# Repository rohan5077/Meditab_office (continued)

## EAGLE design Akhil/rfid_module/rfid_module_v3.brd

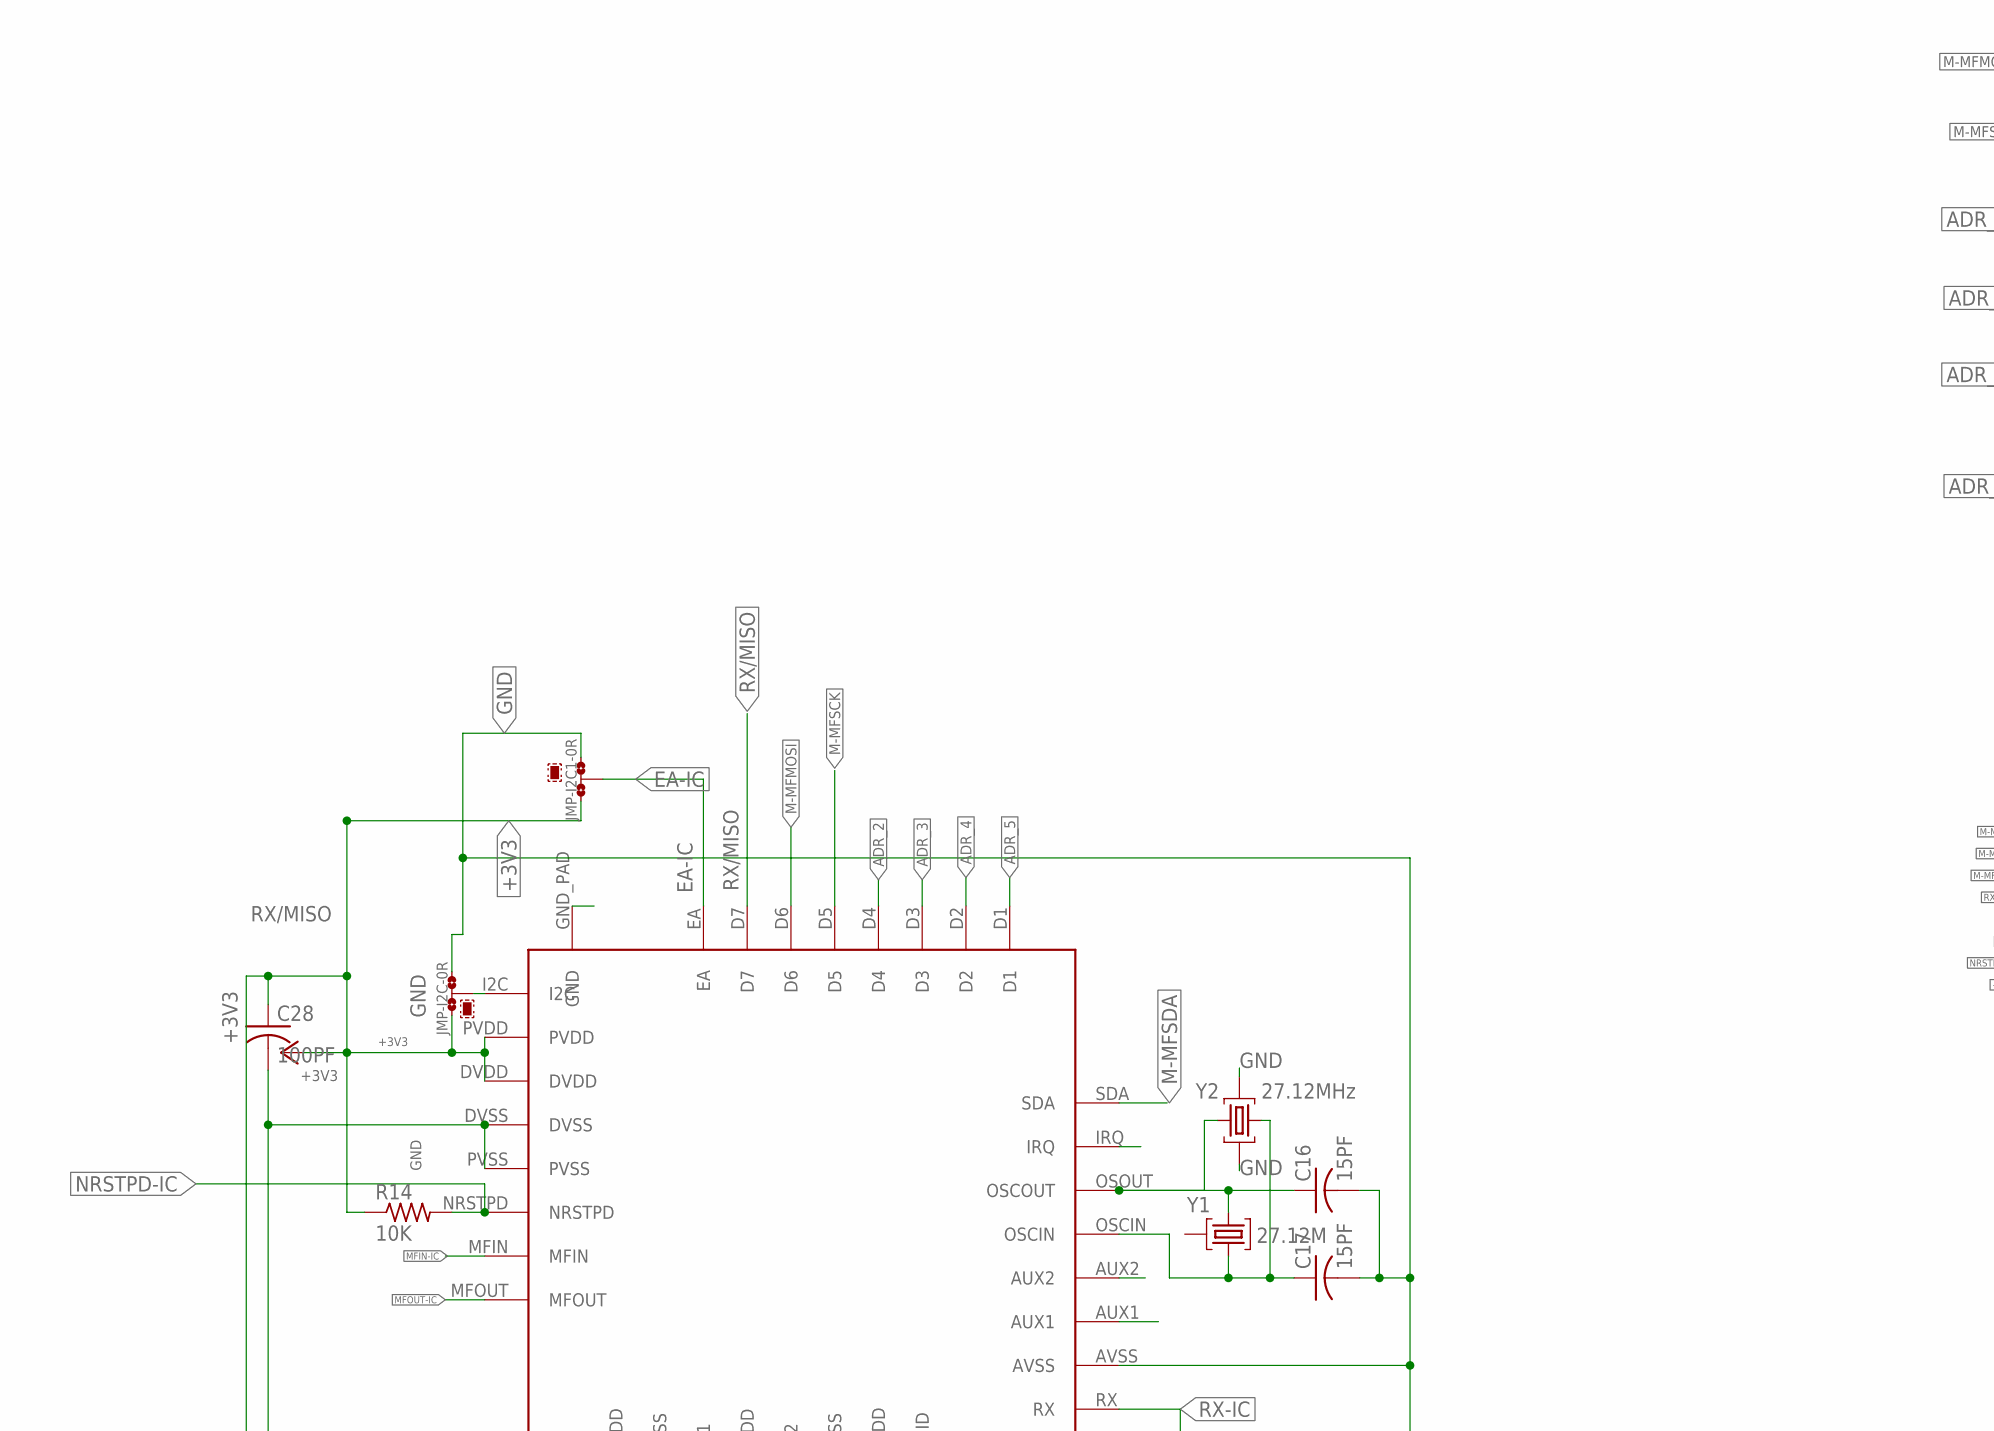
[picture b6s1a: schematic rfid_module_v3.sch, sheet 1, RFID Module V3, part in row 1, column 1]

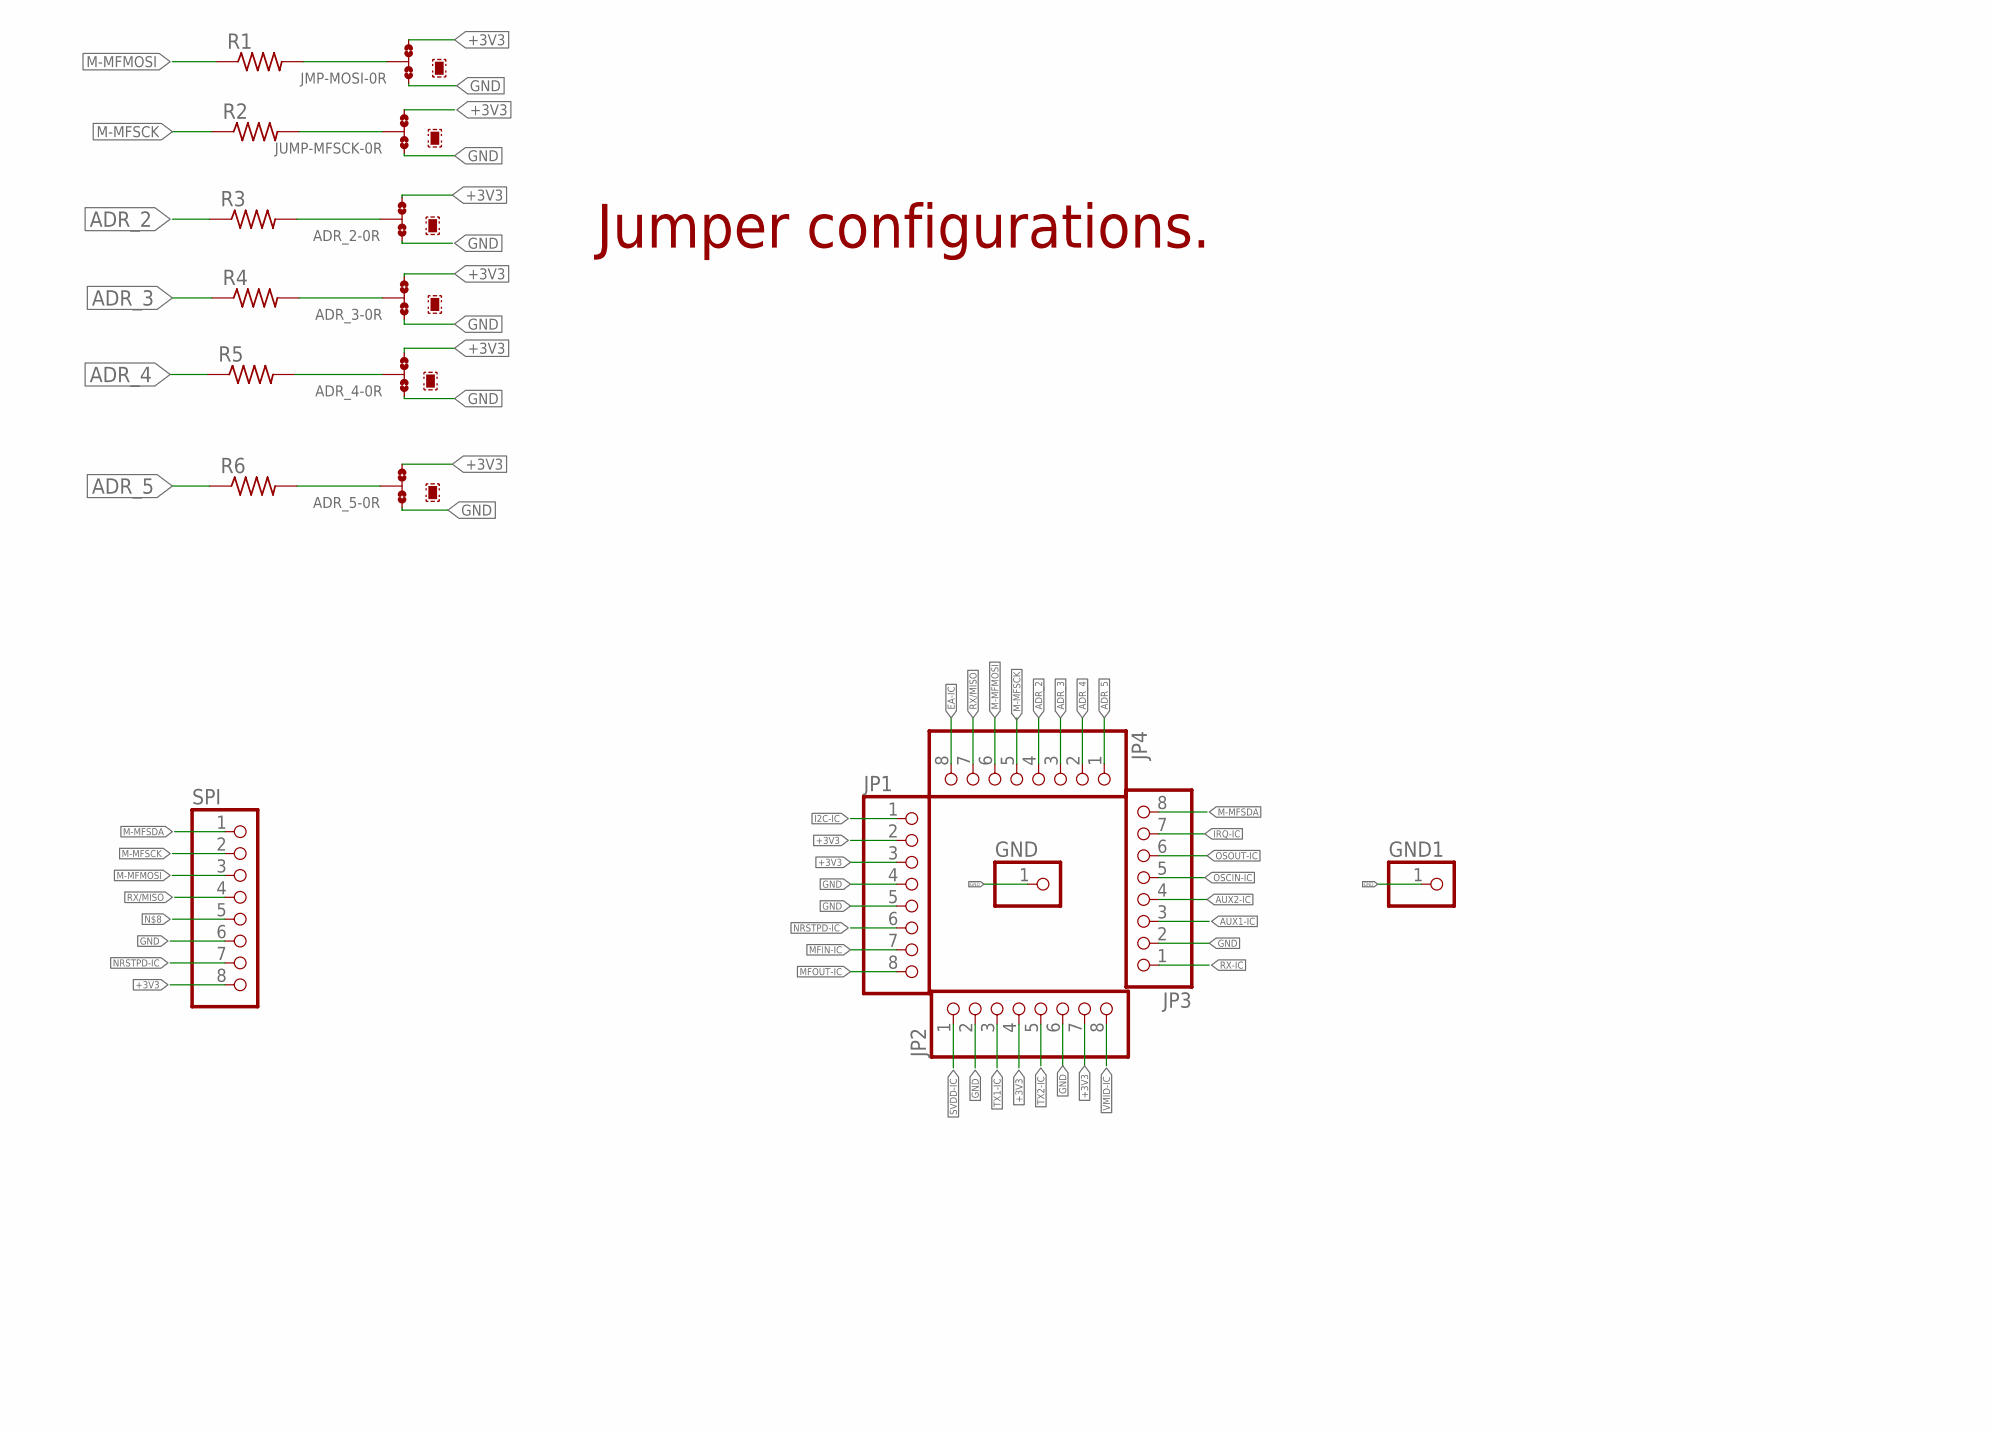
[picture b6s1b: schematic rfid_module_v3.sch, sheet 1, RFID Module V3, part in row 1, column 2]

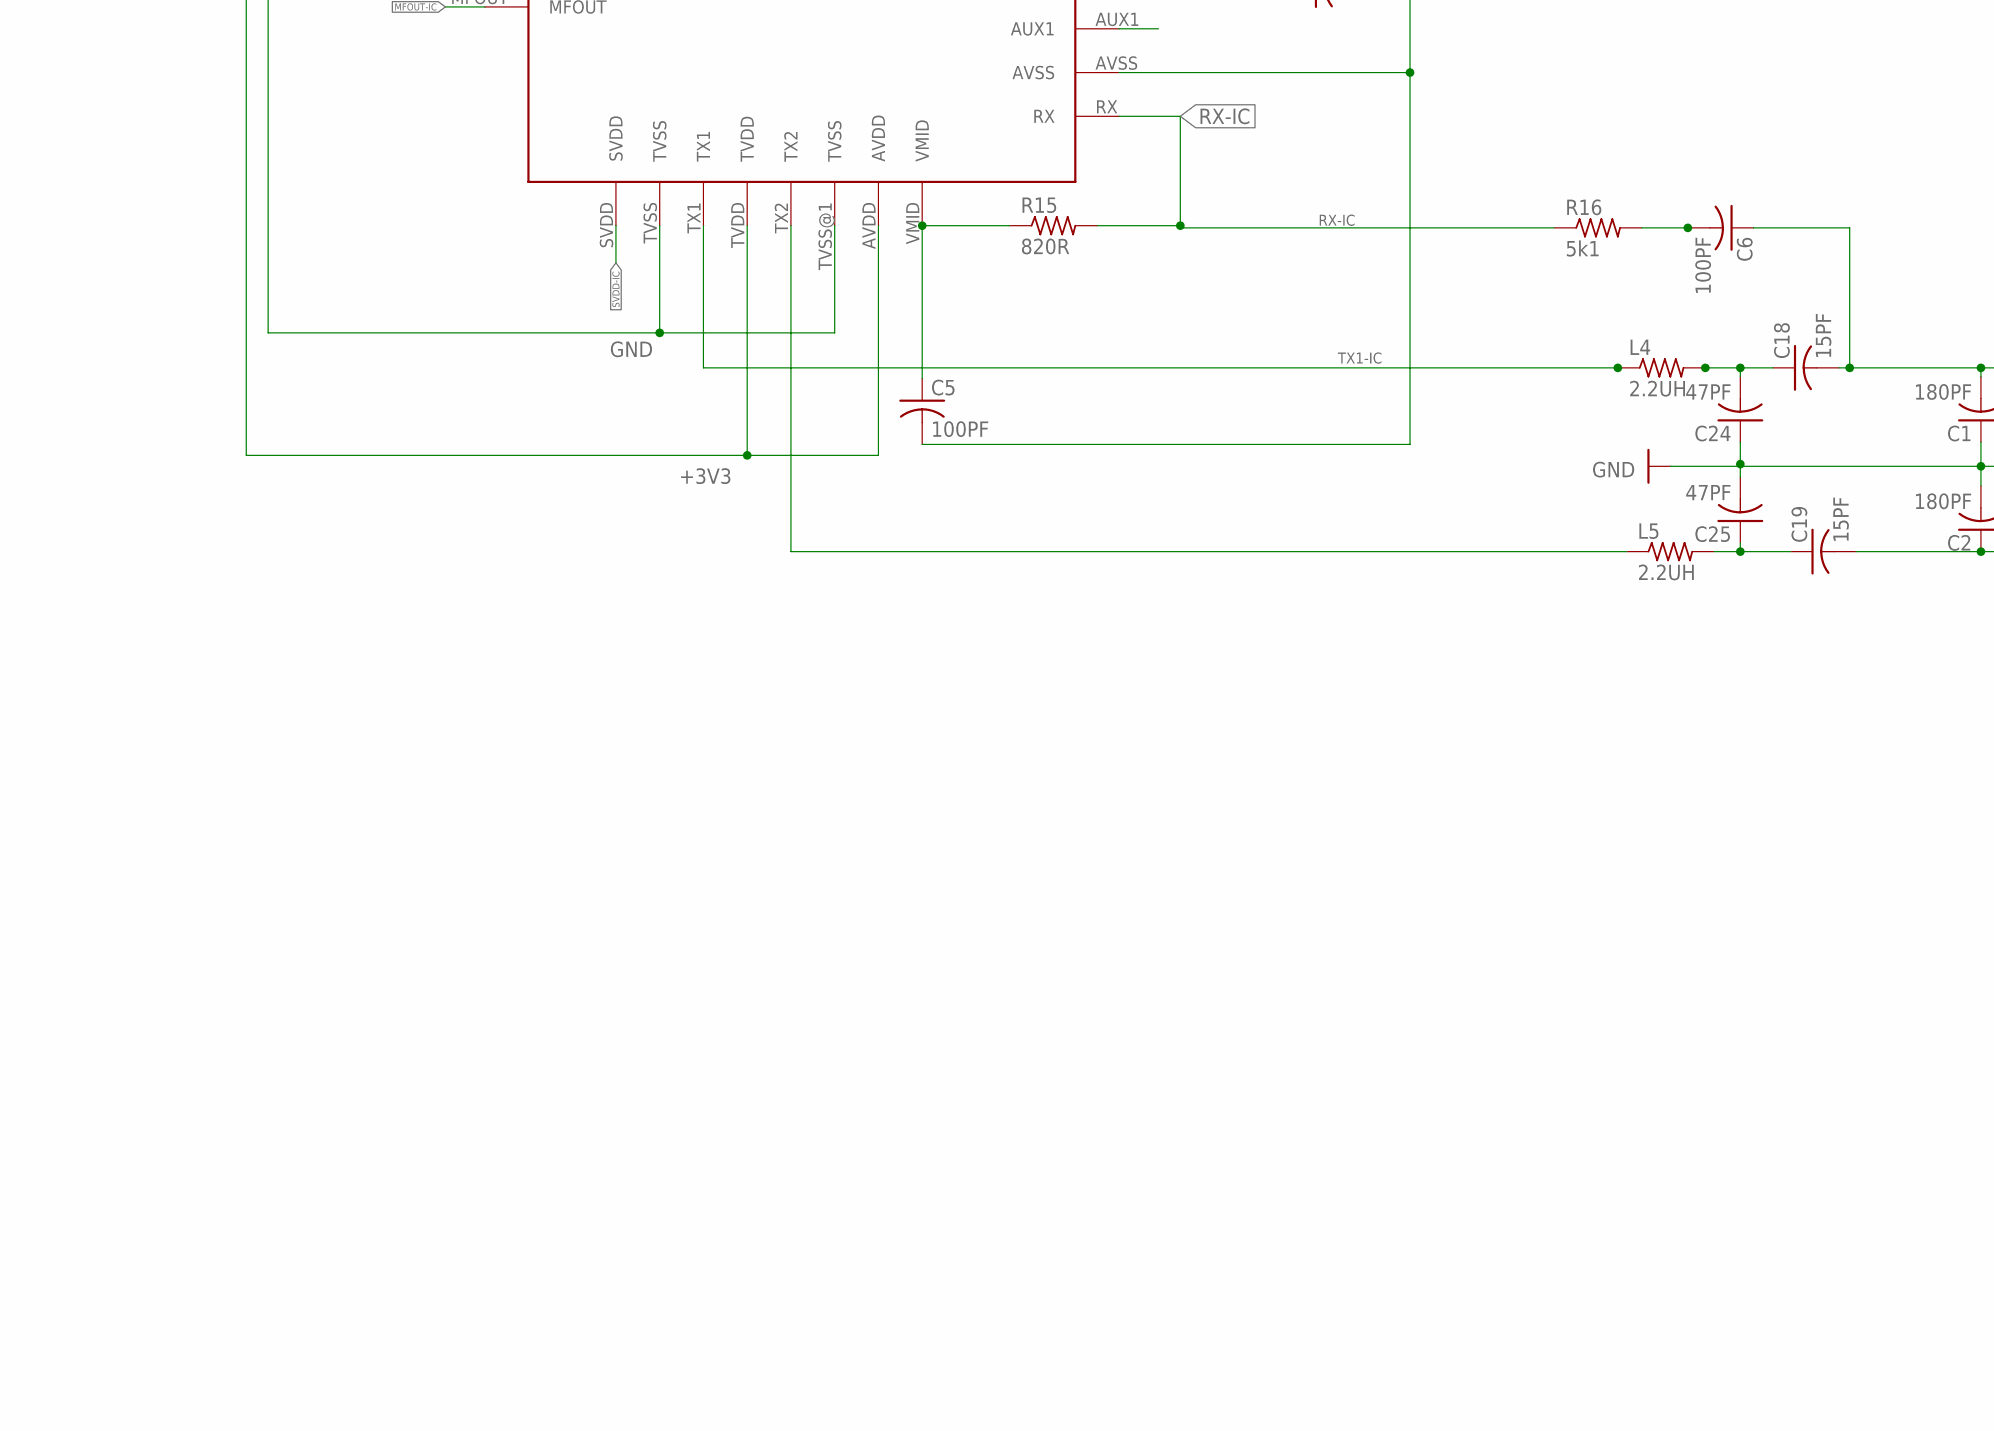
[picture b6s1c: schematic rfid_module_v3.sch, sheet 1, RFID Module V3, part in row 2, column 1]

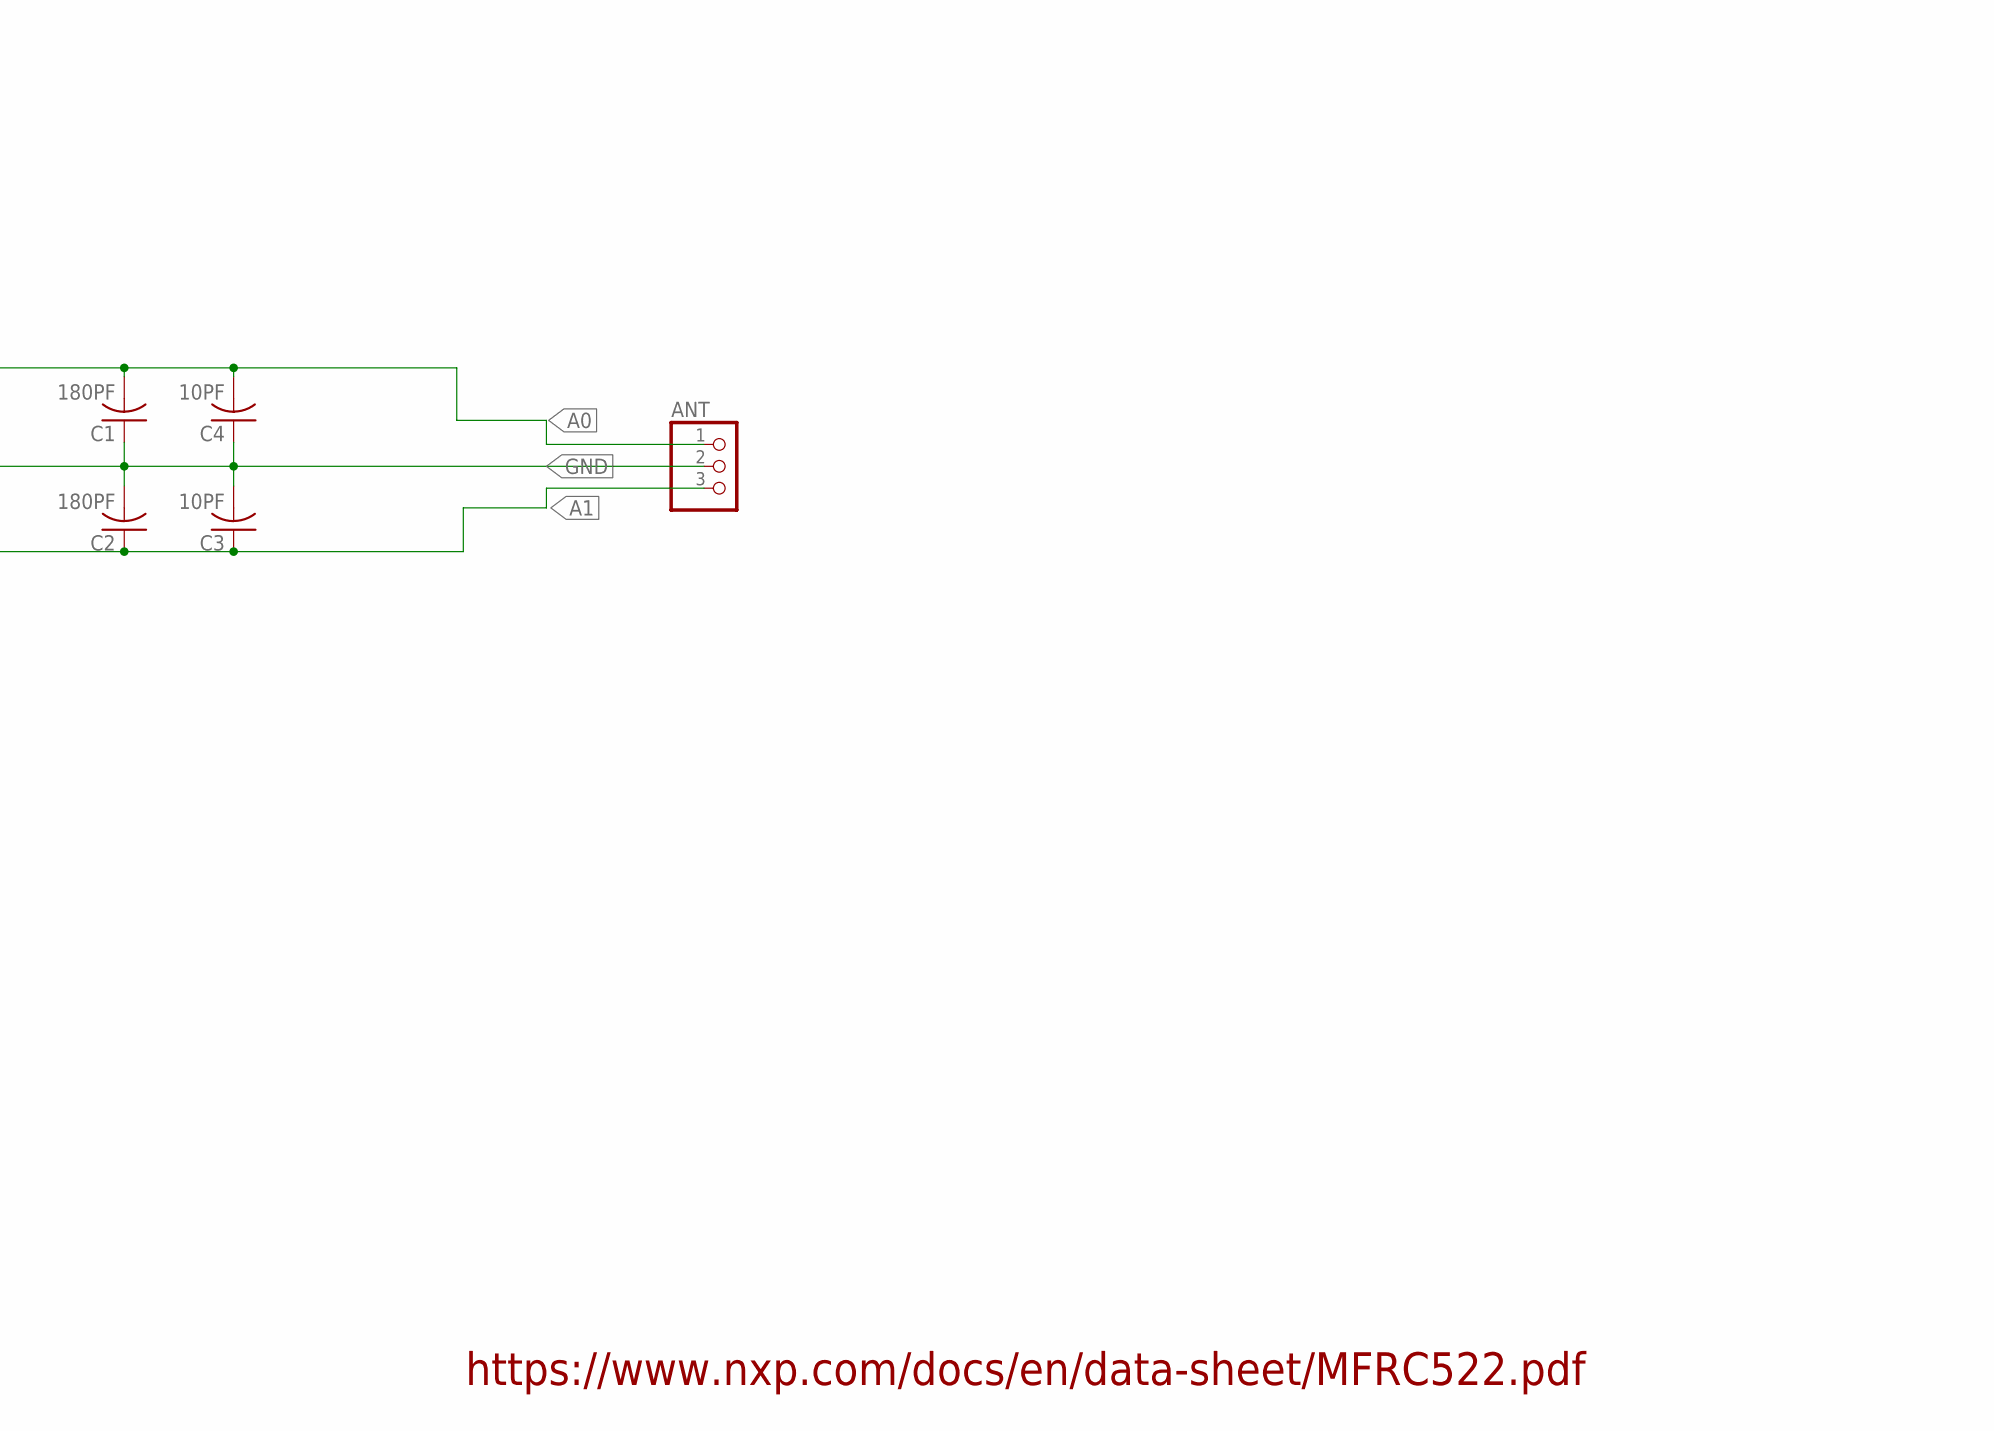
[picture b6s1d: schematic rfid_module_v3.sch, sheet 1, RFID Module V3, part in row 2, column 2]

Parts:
ADR_2, ADR_3, ADR_4, ADR_5: 0R-JUMPA; A0R-JMP
ANT: PINHD-1X3; 1X03
C1, C2: 180PF; C0603
C3, C4: 10PF; C0603
C5, C6, C28: 100PF; C0603
C16, C17, C18, C19: 15PF; C0603
C24, C25: 47PF; C0603
GND, GND1: PINHD-1X1; 1X01
JMP-I2C: 0R-JUMPA; A0R-JMP
JMP-I2C1: JMP-EA; A0R-JMP
JMP-MOSI: 0R-JUMPA; A0R-JMP
JP1, JP2, JP3, JP4: PINHD-1X8; 1X08
JUMP-MFSCK: 0R-JUMPA; A0R-JMP
L4, L5: 2.2UH; R0603
R1, R2, R3, R4, R5, R6: R-US_R0603; R0603
R14: 10K; R0603
R15: 820R; R0603
R16: 5k1; R0603
SPI: PINHD-1X8; 1X08
U$1: MFRC522
Y1: 27.12M; RAD3LEAD
Y2: 27.12MHz; CRYSTAL-3.2-2.5

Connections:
+3V3: ADR_2.3, ADR_3.3, ADR_4.3, ADR_5.3, C28.1, JMP-I2C.3, JMP-I2C1.3, JMP-MOSI.3, JP1.2, JP1.3, JP2.4, JP2.7, JUMP-MFSCK.3, R14.1, SPI.8, U$1.AVDD, U$1.DVDD, U$1.PVDD, U$1.TVDD
A0: ANT.1, C1.2, C4.2, C6.1, C18.2
A1: ANT.3, C2.1, C3.1, C19.2
ADR_2: JP4.4, R3.1, U$1.D4
ADR_3: JP4.3, R4.1, U$1.D3
ADR_4: JP4.2, R5.1, U$1.D2
ADR_5: JP4.1, R6.1, U$1.D1
AUX1-IC: JP3.3, U$1.AUX1
AUX2-IC: JP3.4, U$1.AUX2
EA-IC: JMP-I2C1.2, JP4.8, U$1.EA
GND: ADR_2.1, ADR_3.1, ADR_4.1, ADR_5.1, ANT.2, C1.1, C2.2, C3.2, C4.1, C5.2, C16.2, C17.2, C24.1, C25.2, C28.2, GND.1, GND1.1, JMP-I2C.1, JMP-I2C1.1, JMP-MOSI.1, JP1.4, JP1.5, JP2.2, JP2.6, JP3.2, JUMP-MFSCK.1, SPI.6, U$1.AVSS, U$1.DVSS, U$1.GND_PAD (GND), U$1.PVSS, U$1.TVSS, U$1.TVSS@1 (TVSS), Y2.2 (GND), Y2.4 (GND)
I2C-IC: JMP-I2C.2, JP1.1, U$1.I2C
IRQ-IC: JP3.7, U$1.IRQ
M-MFMOSI: JP4.6, R1.1, SPI.3, U$1.D6
M-MFSCK: JP4.5, R2.1, SPI.2, U$1.D5
M-MFSDA: JP3.8, SPI.1, U$1.SDA
MFIN-IC: JP1.7, U$1.MFIN
MFOUT-IC: JP1.8, U$1.MFOUT
unnamed: C18.1, C24.2, L4.2
unnamed: JMP-MOSI.2, R1.2
unnamed: C19.1, C25.1, L5.2
unnamed: JUMP-MFSCK.2, R2.2
unnamed: C6.2, R16.2
unnamed: ADR_2.2, R3.2
unnamed: ADR_3.2, R4.2
unnamed: ADR_4.2, R5.2
unnamed: ADR_5.2, R6.2
NRSTPD-IC: JP1.6, R14.2, SPI.7, U$1.NRSTPD
OSCIN-IC: C17.1, JP3.5, U$1.OSCIN, Y1.1, Y2.1 (C1)
OSOUT-IC: C16.1, JP3.6, U$1.OSOUT (OSCOUT), Y1.3, Y2.3 (C2)
RX-IC: JP3.1, R15.2, R16.1, U$1.RX
RX/MISO: JP4.7, SPI.4, U$1.D7
SVDD-IC: JP2.1, U$1.SVDD
TX1-IC: JP2.3, L4.1, U$1.TX1
TX2-IC: JP2.5, L5.1, U$1.TX2
VMID-IC: C5.1, JP2.8, R15.1, U$1.VMID

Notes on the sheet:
https://www.nxp.com/docs/en/data-sheet/MFRC522.pdf
Jumper configurations.

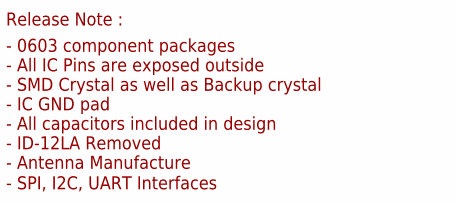
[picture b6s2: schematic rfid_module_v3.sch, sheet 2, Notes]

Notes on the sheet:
Release Note :
- 0603 component packages - All IC Pins are exposed outside - SMD Crystal as well as Backup crystal - IC GND pad - All capacitors included in design - ID-12LA Removed - Antenna Manufacture
- SPI, I2C, UART Interfaces

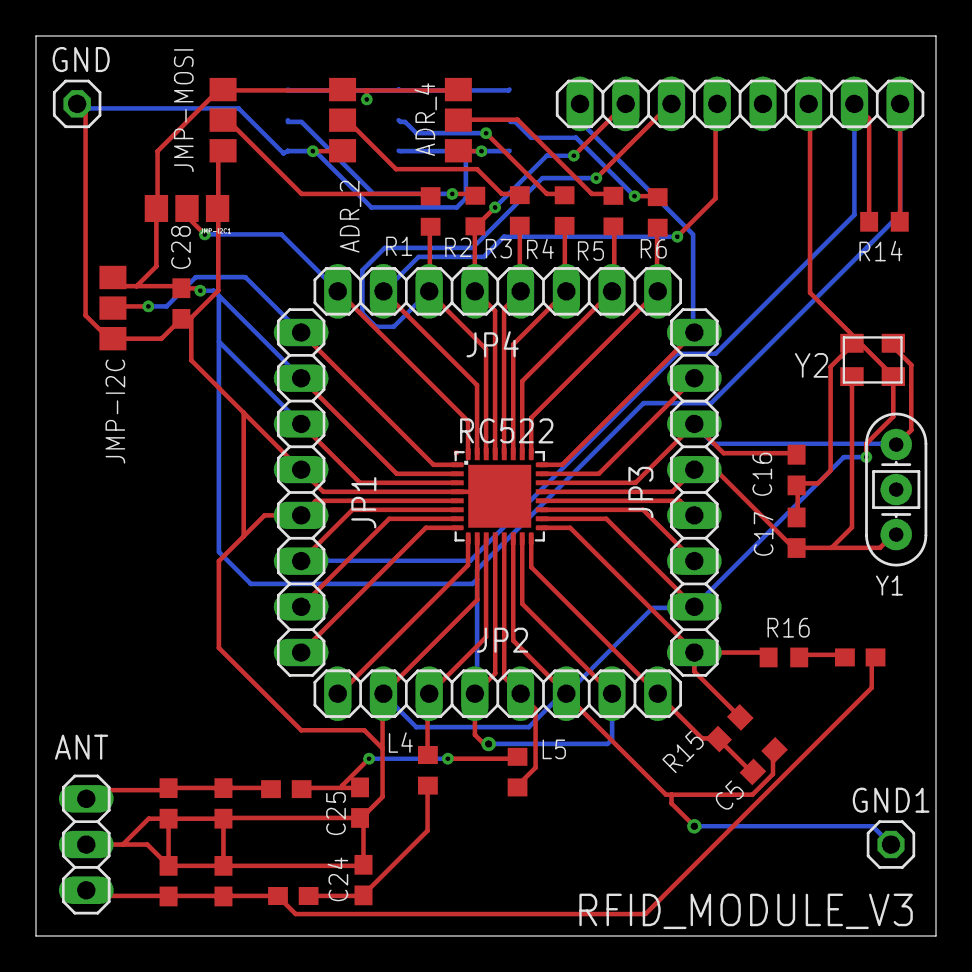
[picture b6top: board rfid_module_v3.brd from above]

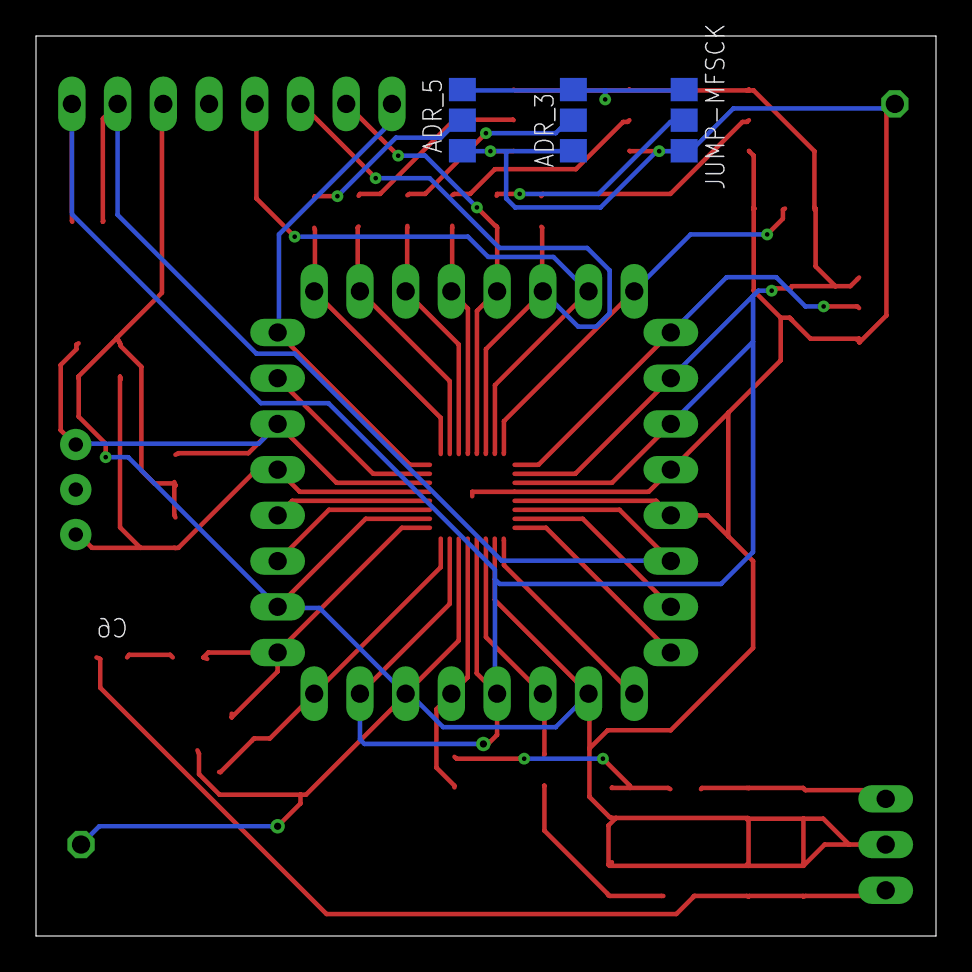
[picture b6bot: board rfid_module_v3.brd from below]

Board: 2 copper layers, 50.0 x 50.0 mm, 43 parts (3 on the bottom side), 36 nets.

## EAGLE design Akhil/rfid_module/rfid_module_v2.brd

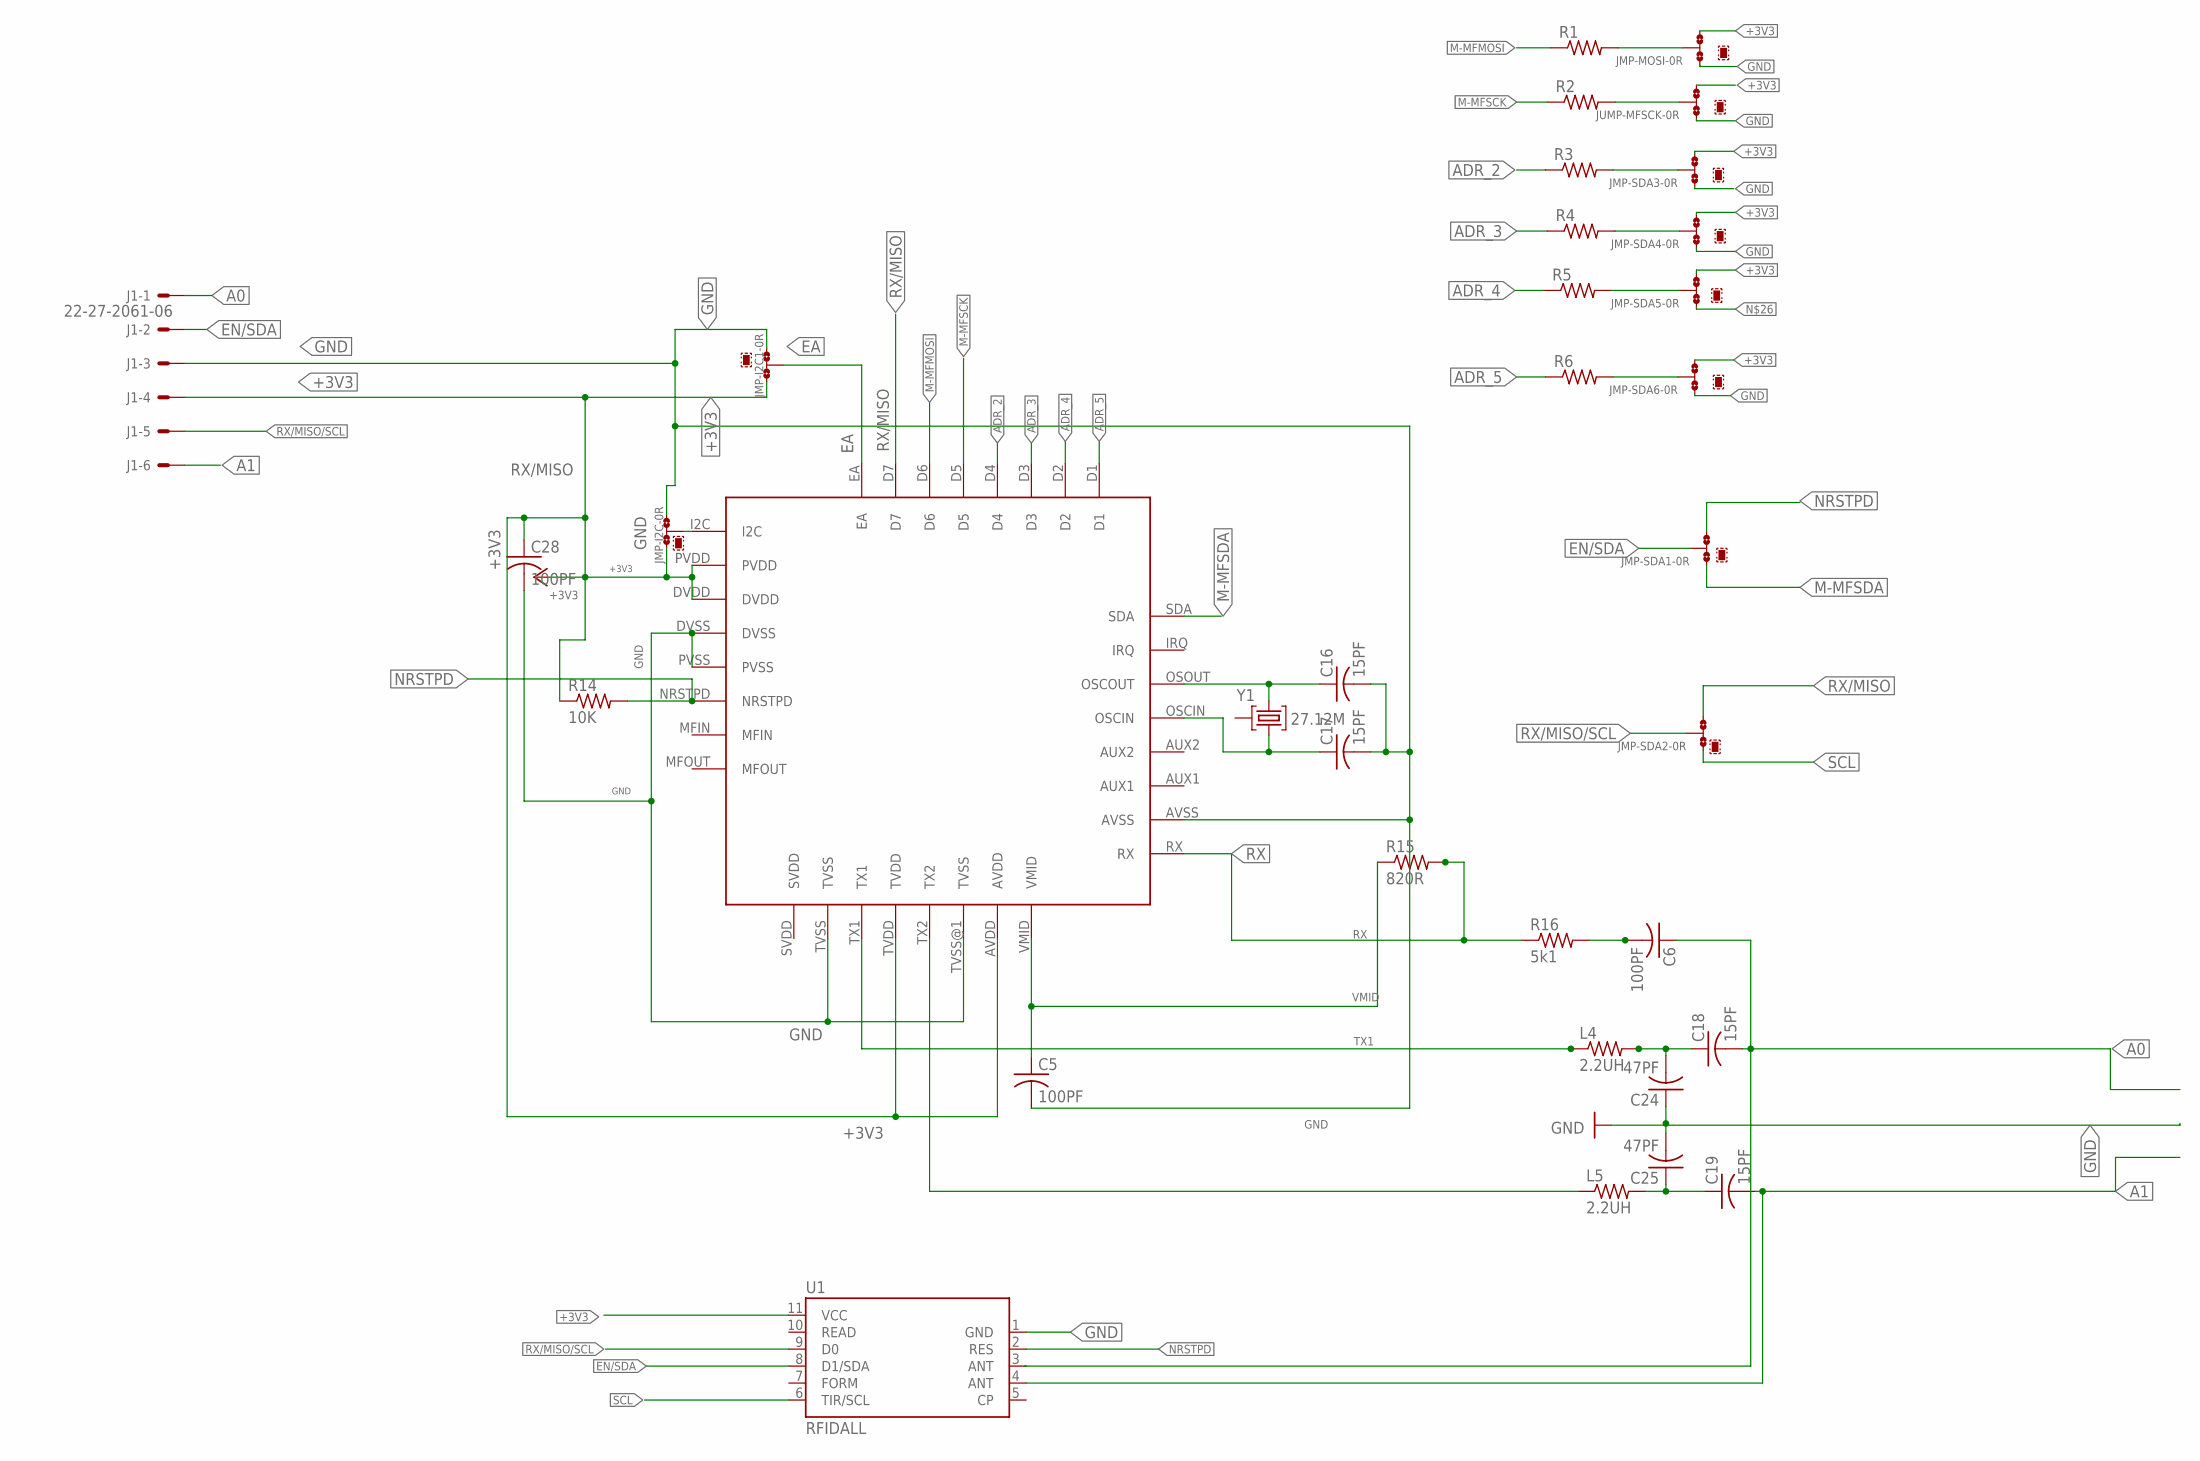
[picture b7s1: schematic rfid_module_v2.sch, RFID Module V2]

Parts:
C5, C6, C28: 100PF; C0402
C16, C17, C18, C19: 15PF; C0402
C24, C25: 47PF; C0402
J1: 22-27-2061-06; 6410-06
JMP-I2C, JMP-I2C1: 0R-JUMPA; A0R-JMP
JMP-MOSI: 0R-JUMPA; A0R-JMP
JMP-SDA1, JMP-SDA2, JMP-SDA3, JMP-SDA4, JMP-SDA5, JMP-SDA6: 0R-JUMPA; A0R-JMP
JUMP-MFSCK: 0R-JUMPA; A0R-JMP
L4, L5: 2.2UH; R0402
R1, R2, R3, R4, R5, R6: R-US_R0402; R0402
R14: 10K; R0402
R15: 820R; R0402
R16: 5k1; R0402
U1: RFIDALL; ID_PACKAGE
U$1: MFRC522
Y1: 27.12M; RAD3LEAD

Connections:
+3V3: C28.1, J1.4, JMP-I2C.3, JMP-I2C1.3, JMP-MOSI.3, JMP-SDA3.3, JMP-SDA4.3, JMP-SDA5.3, JMP-SDA6.3, JUMP-MFSCK.3, R14.1, U1.11 (VCC), U$1.AVDD, U$1.DVDD, U$1.PVDD, U$1.TVDD
A0: C6.1, C18.2, J1.1
A1: C19.2, J1.6, U1.4 (ANT)
ADR_2: R3.1, U$1.D4
ADR_3: R4.1, U$1.D3
ADR_4: R5.1, U$1.D2
ADR_5: R6.1, U$1.D1
EA: JMP-I2C1.2, U$1.EA
EN/SDA: J1.2, JMP-SDA1.2, U1.8 (D1/SDA)
GND: C5.2, C16.2, C17.2, C24.1, C25.2, C28.2, J1.3, JMP-I2C.1, JMP-I2C1.1, JMP-MOSI.1, JMP-SDA3.1, JMP-SDA4.1, JMP-SDA6.1, JUMP-MFSCK.1, U1.1 (GND), U$1.AVSS, U$1.DVSS, U$1.PVSS, U$1.TVSS, U$1.TVSS@1 (TVSS)
M-MFMOSI: R1.1, U$1.D6
M-MFSCK: R2.1, U$1.D5
M-MFSDA: JMP-SDA1.1, U$1.SDA
unnamed: C16.1, U$1.OSOUT (OSCOUT), Y1.3
unnamed: C18.1, C24.2, L4.2
unnamed: C17.1, U$1.OSCIN, Y1.1
unnamed: JMP-MOSI.2, R1.2
unnamed: C19.1, C25.1, L5.2
unnamed: JMP-I2C.2, U$1.I2C
unnamed: L5.1, U$1.TX2
unnamed: JUMP-MFSCK.2, R2.2
unnamed: C6.2, R16.2
unnamed: JMP-SDA3.2, R3.2
unnamed: JMP-SDA4.2, R4.2
unnamed: JMP-SDA5.2, R5.2
unnamed: JMP-SDA6.2, R6.2
NRSTPD: JMP-SDA1.3, R14.2, U1.2 (RES), U$1.NRSTPD
RX: R15.2, R16.1, U$1.RX
RX/MISO: JMP-SDA2.3, U$1.D7
RX/MISO/SCL: J1.5, JMP-SDA2.2, U1.9 (D0)
SCL: JMP-SDA2.1, U1.6 (TIR/SCL)
TX1: L4.1, U$1.TX1
VMID: C5.1, R15.1, U$1.VMID

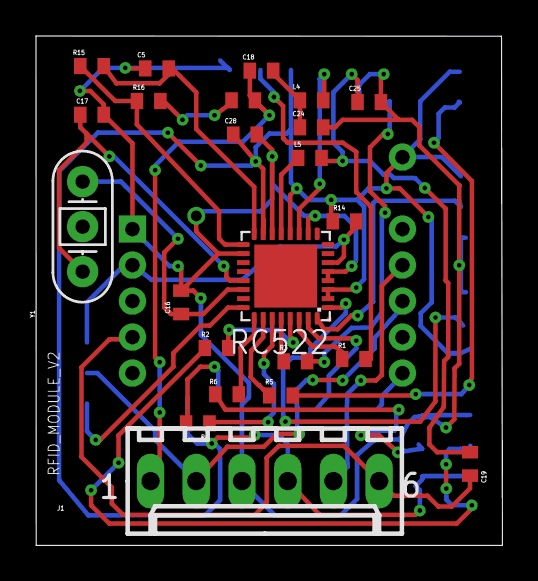
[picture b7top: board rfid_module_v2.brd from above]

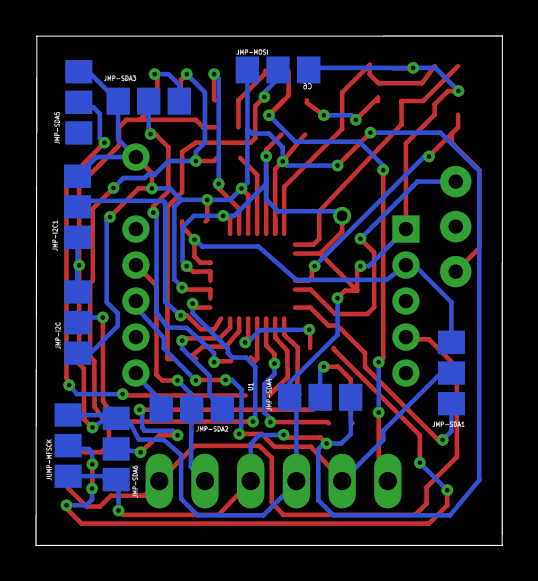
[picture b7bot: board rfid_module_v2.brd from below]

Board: 2 copper layers, 25.9 x 28.3 mm, 34 parts (11 on the bottom side), 33 nets.

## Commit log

2018-06-05 powerstep board
2018-06-06 eagle powerstepproto
2018-06-08 powerstep.brd
2018-06-12 rfid and power_multiIO
2018-06-14 small hopper
